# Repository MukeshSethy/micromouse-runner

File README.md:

# Micromouse Runner

A competition-style micromouse robot on a custom **100 × 120 mm, 4-layer**
KiCad 10 PCB: ESP32-S3 module doing all control + wireless telemetry, a 2S
power tree with a regulated 6 V motor rail, a BNO055 9-axis IMU, research-
verified sensor geometry, and a fully script-generated, fully autorouted design.

 > **Status (2026-07-20, rev 7.2): all requirements closed — fab-ready, order-ready.**
> `verify_drc.py` PASS: **0 errors / 0 warnings / 0 unconnected / 0 parity /
> ratsnest 0** (error-inclusive severity — never use `--severity-warning`,
> it hides errors on KiCad 10.0.4). Final battery: **12/12 green** (ERC,
> netlist gates, 41 circuit tests, 30-pin fw gate, flash/preflight/power/hw/
> line sims incl. IMU self-test coverage, 4/4 negative tests, DRC).
> Rev 7.2 adds: **XT60 battery input** (parallel with JST-XH, ONE PACK ONLY),
> **buzzer on IO46**, **JST-ZH motor connectors** (the robu GA12-N20 factory
> plug goes straight in — zero soldering), optional balance lead, selective
> silk refdes + assembly-PDF debug maps. Production folders for **Lion
> Circuits** ([`pcb/LionCircuit_4layers/`](pcb/LionCircuit_4layers/)) and
> **JLCPCB** ([`pcb/JLCPCB_4layers/`](pcb/JLCPCB_4layers/)). A leaner
> **2-layer, fully JLC-assemblable** edition (line sensors removed) is under
> construction at [`pcb/JLCPCB_2layers/`](pcb/JLCPCB_2layers/). Each project
> folder is self-contained: `design/`, `production/`, `fw/`, `simulation/`,
> `images/`.

**Top** — sensors, module, connectors (motor plugs go straight into J5/J6):

**Bottom** — ground pour, USB ESD cluster, button-side routing:

## The board (rev 7)

| Subsystem | Part | Notes |
|---|---|---|
| Controller | ESP32-S3-WROOM-1-N8R2 (bare module, dual-core FreeRTOS) | Rear placement; antenna spans a rear-edge U-notch (Espressif fallback), tip inside the board |
| Motor driver | TB6612FNG bare SSOP-24, **IN/IN PWM mode** | 6 V VM rail; PWMA/PWMB/STBY tied high, the four IN pins carry LEDC |
| **Power** | **2S LiPo** → **AP63203** (3.3 V/2 A logic) + **TPS54302** (regulated **6.0 V**/3 A motors) | Fuse 3.5 A/16 V PPTC (rev 7.1), DMP3098L reverse P-FET (Vgs ±20 V), balance-tap per-cell monitoring (optional — fw auto-detects); battery via JST-XH **or** XT60 (rev 7.2, ONE PACK ONLY) |
| **Switches** | **SW5 = PWR ALL** (logic EN) + **SW6 = PWR MOTORS** (6 V rail EN) | Motors need both on; SW6's pull-up feeds from the SW5 node |
| **IMU** | **BNO055 9-axis** on the centerline, I2C (IO18/21), INT IO37 | Internal oscillator; gyro drives the yaw loop |
| Wall sensors | 6× IR333-A + PT334-6B pairs: front **0°**, diagonal **45.0°**, side **90.0°** | Exact aims with silk angle callouts; bent-body outlines fully inside the board (3–5 mm edge gap) |
| Line sensors | 8× Vishay TCRT5000, 9.525 mm QTR pitch, bottom face | Read through a CD74HC4067 mux (+ battery/VBUS telemetry on spare channels); walls go **direct to ADC1** |
| Indicators | Per-sensor LEDs on top for all 8 line + 6 wall channels | Wall LED ON = wall seen |
| User I/O | Buttons **A / B / C** (+ RST) lettered on silk; two power slides | A doubles as BOOT |
| USB | USB-C at the rear (flash/debug), ESD-protected, VBUS cable-detect | Direct D± (no series R, Espressif practice); 1×6 JTAG header |

All parts are orderable from **Lion Circuits** (verified In-Stock, 2026-07);
see [`pcb/STANDARDS.md`](pcb/STANDARDS.md) for the impedance / IPC / Espressif
compliance write-up.

Drive wheels run in open edge notches (wheel/tyre width unconstrained);
front castor hole at the nose. Chamfered nose for the diagonal sensor pair.

### 3D-printable motor bracket

Print two of the UKMARSBot **Pololu-pattern N20 bracket** (MIT licence):
[`pololu-gear-motor-bracket-standard.stl`](https://raw.githubusercontent.com/ukmars/ukmarsbot/master/mechanical/pololu-gear-motor-bracket-standard.stl)
(from [github.com/ukmars/ukmarsbot](https://github.com/ukmars/ukmarsbot),
`mechanical/`). The board is drilled for it: Ø3.2 mm NPTH pairs at 18.0 mm
centres — (17.25, 75)/(17.25, 93) and (82.75, 75)/(82.75, 93), axle at y = 84.
M2/M2.5/M3 screws from the underside into nuts captured by the bracket.

## Design rules & tooling

- 0.3 mm clearance against **every through-hole pin** on every verification
  path (hand-solder safety, structural in the router); SMD fields may relax
  to 0.16 mm where physics demands it.
- GND poured on F.Cu (full board) + B.Cu (remainder) + the In1 plane; In2 =
  3V3 plane; VM_BATT/VM_6V as priority-1 B.Cu islands; SMD pour pads stitched.
- Routed to **zero unrouted edges** by the project's own 4-layer A*
  autorouter (`route_loaded.py`): jailed-first ordering with immediate retry
  ladders, hand-computed bridges for the USB-C pad field, wide
  "verify-proof" retry rungs, and a convergent DRC heal loop
  (`heal_all.py`). The war stories live in `pcb/PROJECT_NOTES.md`.

## Repository layout

```
micromouse-runner/
├── pcb/            KiCad hardware design
│   ├── micromouse-pcb.kicad_sch / .kicad_pcb / .kicad_pro
│   ├── netlist.net
│   ├── CONNECTIONS.md      every net, every pin, and why (generated, coverage-enforced)
│   ├── PROJECT_NOTES.md    full design decision log, research, and known issues
│   ├── n20.pretty/         hand-authored exact N20 motor footprint + 3D model
│   └── tools/              generators (schematic + PCB are script-produced, so auditable)
│       ├── gen_sch.py / build_schematic.py     schematic generator
│       ├── gen_pcb.py / build_pcb.py           placement + in-house N-layer A* autorouter
│       ├── board_geom.py                       single source of mechanical truth
│       ├── route_loaded.py                     routing pipeline (run build_pcb.py first)
│       ├── heal_all.py                         convergent DRC-unconnected healer
│       └── gen_connections.py / verify_netlist.py   docs + connectivity checks
├── fw/             sample firmware + host simulation
│   ├── micromouse/     pins.h (netlist-gated) + control_core + .ino (line following)
│   ├── sim/            gcc host sim of the EXACT control core (scenarios asserted)
│   └── check_pins.py   gate: every firmware pin verified against the netlist
├── simulation/     maze-solving / motion simulation — planned
└── images/         renders
```

## Verification

- `pcb/TEST_REPORT.md` — **41** analytical circuit tests computed from the
  netlist (2S power tree, both bucks + the dual-switch enable logic, IN/IN
  motor drive, IMU I2C, mux telemetry, flashing/straps/JTAG, every IR chain),
  100 % net + component coverage. The harness **caught a real design bug**
  (the motor rail could never enable — R69's 1 MΩ source impedance sagged the
  EN divider; fixed).
- `pcb/STANDARDS.md` — impedance / IPC-2221B / IPC-2152 / grounding /
  Espressif antenna compliance, with numbers (USB-FS is not a
  controlled-impedance case; the 90 Ω rule is high-speed-only).
- `pcb/TRACE_REPORT.md` — trace-level copper analysis of the routed board:
  per-net path resistance, IR drops at operating currents, via ampacity, USB
  skew.
- `fw/sim/` — the shipped control core runs against board-derived physics;
  the sim caught two real control bugs before hardware. All scenarios pass.
- `pcb/CONNECTIONS.md` — the per-trace justification document: every net,
  every pin, and why (generated, coverage-enforced).

> **Connectivity note:** `kicad-cli pcb drc` under-reports unconnected items
> headless; the project gates on the **pcbnew ratsnest** (`GetUnconnectedCount`
> after a zone fill), and `finalize.py` refuses to strip copper unless that
> ratsnest is already zero.

## Ordering / fabrication

- `pcb/BOM.csv` — every row a verified MPN **In-Stock at Lion Circuits**
  (turnkey from Digi-Key/Mouser/Element14/Arrow/Avnet/RS). Power: AP63203WU-7,
  TPS54302DDCR, DMP3098L-7, MINISMDC260F/16-2, SRP4020TA-4R7M, EEE-FT1C221AP.
  IMU: BNO055. Optics: IR333-A + PT334-6B + TCRT5000. Connectors/switches:
  USB4105-GF-A, B2B-XH-A, PCM12SMTR, PTS645VL582LFS.
- `pcb/tools/export_fab.py` regenerates `pcb/fab/`: gerbers, Excellon drill
  (bracket/castor NPTH tools asserted present), placement CSV, and a fit-check
  STEP that loads **every** 3D model (project-local box-true models for the
  N20 motors, BNO055 and the SRP4020TA inductors).

## Build / regenerate

The PCB tooling runs from `pcb/` using the KiCad-bundled Python (`pcbnew`);
see `pcb/PROJECT_NOTES.md` for exact commands and the many hard-won
KiCad-format notes. Regeneration order: `build_schematic.py` → export
netlist → `verify_netlist.py` → `build_pcb.py` → `route_loaded.py` →
`heal_all.py` → `finalize.py` (silk→fab + ratsnest-gated stub cleanup) →
`sync_board_meta.py` (parity metadata) → `export_fab.py`.

> **Warning:** the shipped rev-7 board was refined **in-place** after routing;
> regenerating overwrites it with a re-route that must then re-pass
> `pcb/tools/verify_drc.py`. Do not regenerate casually — the committed
> `.kicad_pcb` is the verified artifact.

## Status

**Rev 7 ships fully routed and verified — all requirements closed.**
`verify_drc.py` PASS: 0 errors / 0 warnings / 0 unconnected / 0 parity /
ratsnest 0 · ERC 0 · 41/41 circuit tests · 29/29 pins · sim ALL PASS ·
export_fab ALL GATES. 2S power with a regulated 6 V motor rail, dual switches,
BNO055 IMU on the centre line, exact 0/45/90° wall-sensor aims with the front
sensors nested in the line-array gaps, indicators behind the sensors, ESP32
decoupling at the pin, ground poured on every possible layer, and a Lion
Circuits-orderable BOM. Formal requirement tracking:
[`pcb/REQUIREMENTS.md`](pcb/REQUIREMENTS.md).

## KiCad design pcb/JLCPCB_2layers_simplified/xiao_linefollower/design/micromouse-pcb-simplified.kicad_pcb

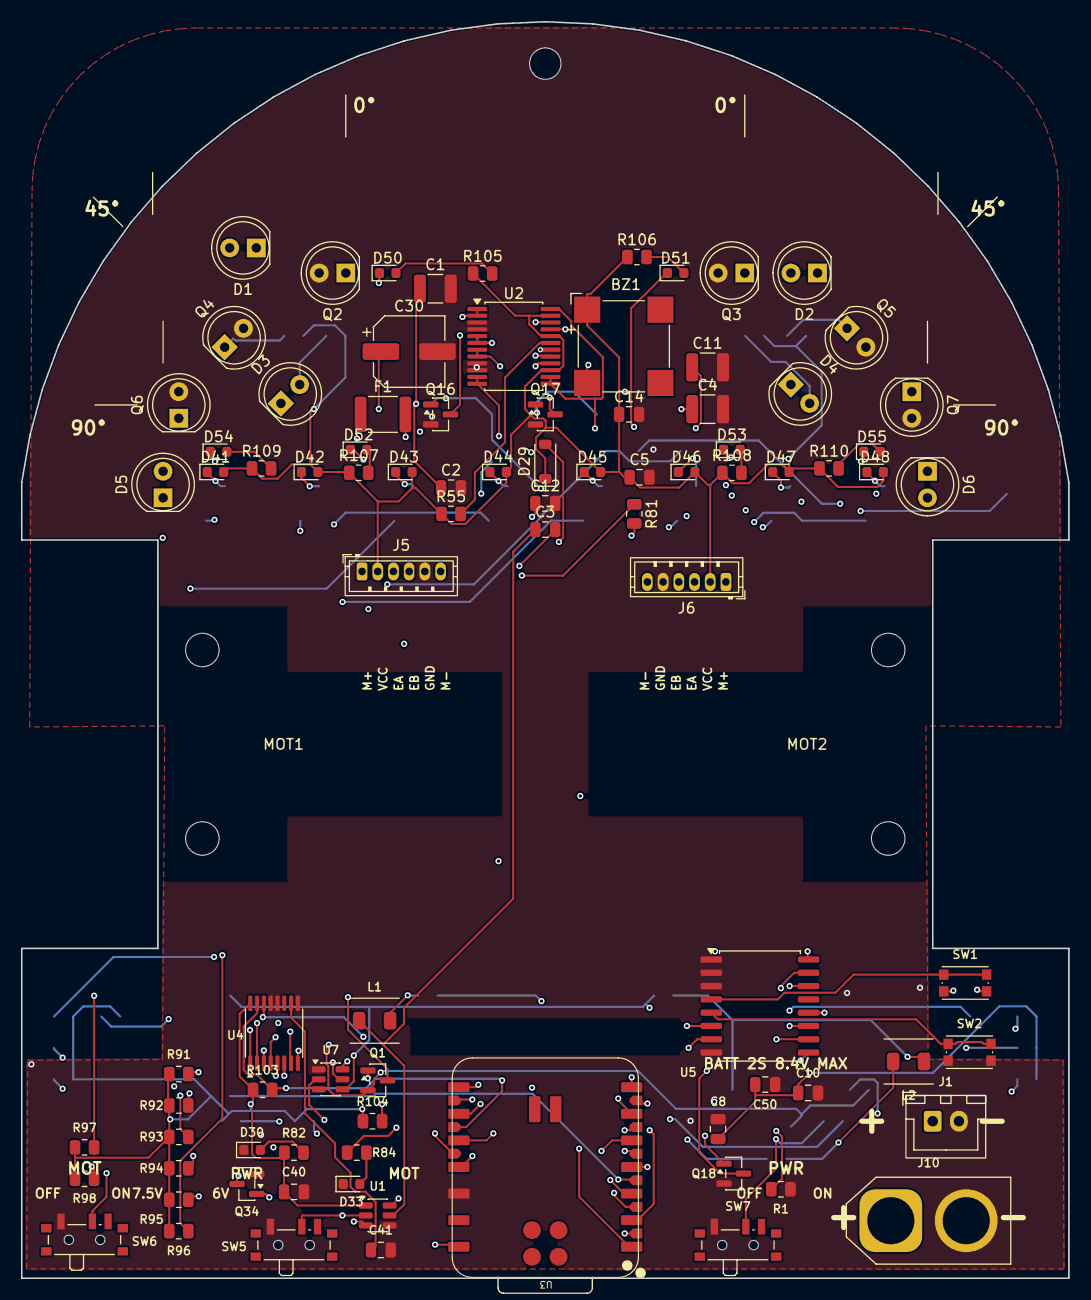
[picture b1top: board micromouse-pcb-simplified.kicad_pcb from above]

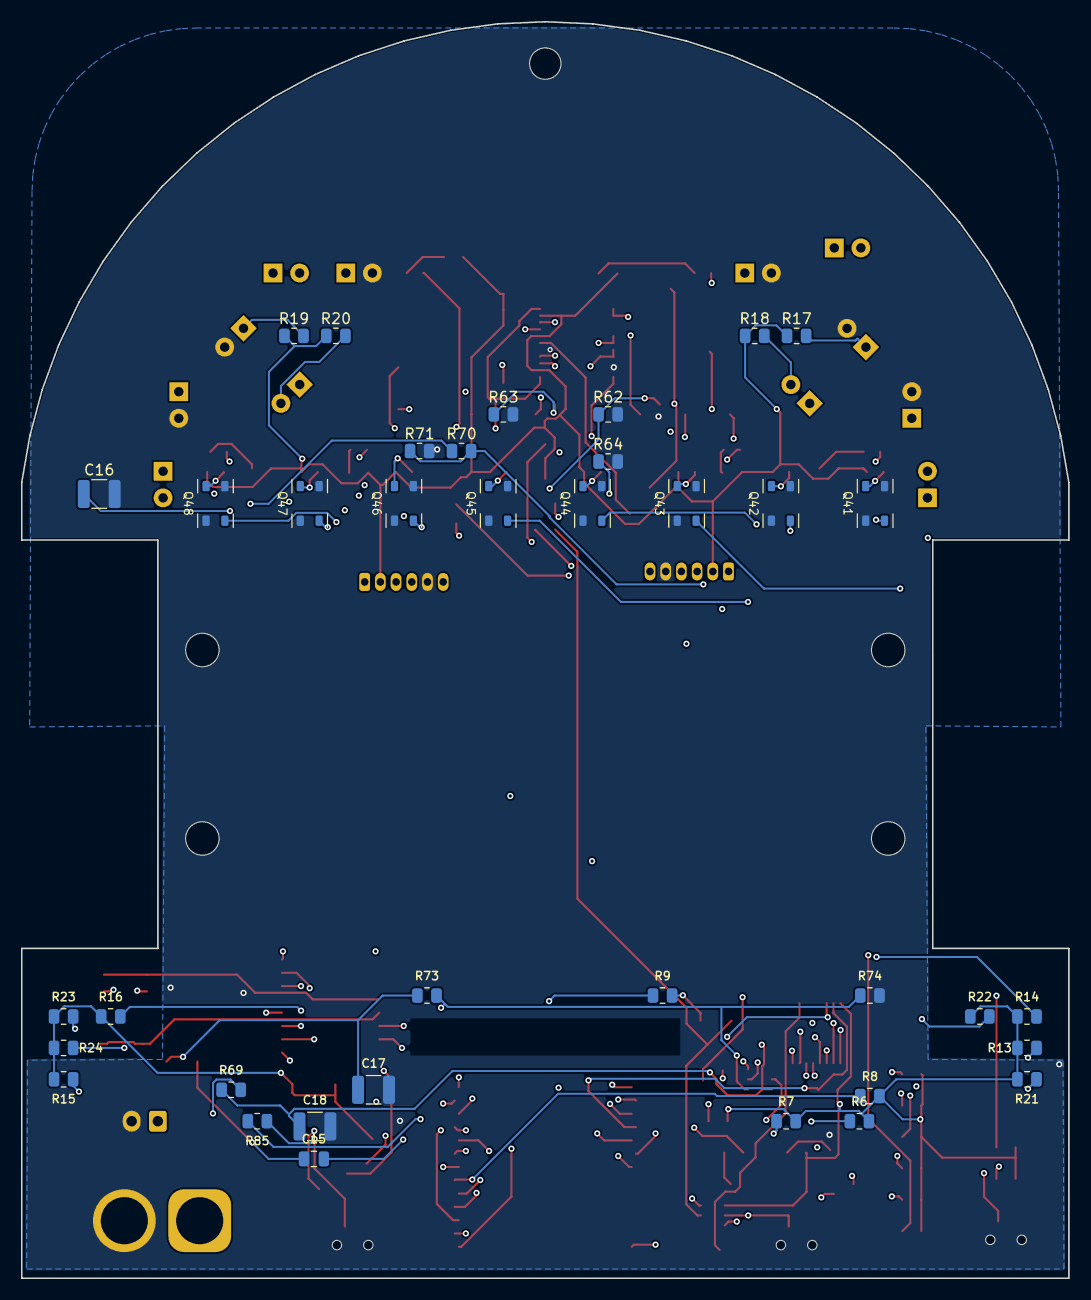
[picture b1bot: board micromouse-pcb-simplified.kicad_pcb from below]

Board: 4 copper layers, 100.0 x 120.0 mm, 133 parts (38 on the bottom side), 84 nets.

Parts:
BZ1: MagneticBuzzer_CUI_CMT-8504-100-SMT
C1, C4, C11, C18: 10uF/25V; C_1210_3225Metric
C2, C3, C12, C14, C15: 100nF; C_0805_2012Metric
C5: 22uF; C_0805_2012Metric
C8, C10, C40, C41, C50: C_0805_2012Metric
C16, C17: 22uF/25V; C_1210_3225Metric
C30: 220uF/16V; CP_Elec_6.3x7.7
CW1: CastorWheel
D1, D2, D3, D4, D5, D6: LED_D5.0mm_IRGrey
D29: D_SOD-123
D30, D33, D41, D42, D43, D44, D45, D46, D47, D48: LED_0603_1608Metric
D50, D51, D52, D53, D54, D55: APT1608SGC; LED_0603_1608Metric
F1: Fuse_1812_4532Metric
H1, H2, H3, H4, H5: MountingHole_NPTH
J1: JST_XH_B2B-XH-A_1x02_P2.50mm_Vertical
J5, J6: JST_ZH_B6B-ZR_1x06_P1.50mm_Vertical
J10: AMASS_XT60-M_1x02_P7.20mm_Vertical
L1, L2: 4.7uH; L_Bourns_SRP4020TA
MOT1, MOT2: N20_Motor_Encoder
Q1, Q16, Q17, Q18, Q34: SOT-23
Q2, Q3, Q4, Q5, Q6, Q7: LED_D5.0mm_IRBlack
Q41, Q42, Q43, Q44, Q45, Q46, Q47, Q48: VAL; QRE1113GR
R1, R6, R7, R8, R9, R13, R14, R15, R16, R17, R18, R19, R20, R21, R22, R23, R24, R55, R62, R63, R64, R69, R70, R71, R73, R74, R81, R82, R84, R85, R91, R92, R93, R94, R95, R96, R97, R98, R103, R104: R_0805_2012Metric
R105, R106, R107, R108, R109, R110: 220; R_0805_2012Metric
SW1, SW2: SW_Push_1P1T_NO_CK_KMR2
SW5, SW6, SW7: SW_SPDT_PCM12
U1: TSOT-23-6
U2: SSOP-24_5.3x8.2mm_P0.65mm
U3: XIAO-nRF52840-Plus-SMD
U4: TSSOP-16_4.4x5mm_P0.65mm
U5: SOIC-16W_7.5x10.3mm_P1.27mm
U7: SOT-23-6

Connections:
AIN1: U2.21, U3.7
AIN2: U2.22, U3.8
BATT_RAW: F1.1, J1.1, J10.1
BIN1: U2.17, U3.9
BIN2: U2.16, U3.10
BUZZ_CTRL: R81.1, U3.11
BUZZ_DRV: BZ1.2, D29.2, Q34.3
EMIT_DIAG_K: D3.1, D4.1, Q17.3
EMIT_FRONT_K: D1.1, D2.1, Q16.3
EMIT_SIDE_K: D5.1, D6.1, Q18.3
ENC1_A: J5.3, R6.1, U3.15
ENC1_B: J5.4, R7.1, U3.16
ENC2_A: J6.3, R8.1, U3.17
ENC2_B: J6.4, R9.1, U3.18
FB_6V: R73.2, R74.1, R85.1, U7.4
GND: C1.2, C2.2, C4.2, C5.2, C8.2, C10.2, C11.2, C12.2, C14.2, C16.2, C17.2, C18.2, C30.2, C40.2, C41.2, C50.2, D30.1, D33.1, J1.2, J5.5, J6.5, J10.2, Q2.2, Q3.2, Q4.2, Q5.2, Q6.2, Q7.2, Q16.2, Q17.2, Q18.2, Q34.2, Q41.2, Q41.4, Q42.2, Q42.4, Q43.2, Q43.4, Q44.2, Q44.4, Q45.2, Q45.4, Q46.2, Q46.4, Q47.2, Q47.4, Q48.2, Q48.4, R1.2, R62.2, R63.2, R64.2, R71.2, R74.2, SW1.2, SW2.2, SW5.1, SW6.1, SW7.1, U1.4, U2.3, U2.4, U2.9, U2.10, U2.18, U3.12, U4.9, U4.12, U4.13, U5.1, U5.2, U5.3, U5.8, U7.1
LINE0_ADC: D41.1, Q41.3, U4.1
LINE1_ADC: D42.1, Q42.3, U4.2
LINE2_ADC: D43.1, Q43.3, U4.3
LINE3_ADC: D44.1, Q44.3, U4.4
LINE4_ADC: D45.1, Q45.3, U4.5
LINE5_ADC: D46.1, Q46.3, U4.6
LINE6_ADC: D47.1, Q47.3, U4.7
LINE7_ADC: D48.1, Q48.3, U4.8
MOTA_N: J5.6, U2.5, U2.6
MOTA_P: J5.1, U2.1, U2.2
MOTB_N: J6.6, U2.7, U2.8
MOTB_P: J6.1, U2.11, U2.12
MOTLED_A: D33.2, R84.2
MOT_EN: R70.2, R71.1, SW6.2, U7.5
unnamed: D1.2, R14.2
unnamed: D2.2, R16.2
unnamed: D3.2, R18.2
unnamed: D4.2, R20.2
unnamed: D5.2, R22.2
unnamed: D6.2, R24.2
unnamed: D50.2, R105.2
unnamed: D51.2, R106.2
unnamed: D52.2, R107.2
unnamed: D53.2, R108.2
unnamed: D54.2, R109.2
unnamed: D55.2, R110.2
unnamed: F1.2, Q1.3
unnamed: Q1.1, R1.1
unnamed: Q34.1, R81.2
unnamed: Q41.1, R91.2
unnamed: Q42.1, R92.2
unnamed: Q43.1, R93.2
unnamed: Q44.1, R94.2
unnamed: Q45.1, R95.2
unnamed: Q46.1, R96.2
unnamed: Q47.1, R97.2
unnamed: Q48.1, R98.2
unnamed: R85.2, SW7.2
unnamed: C3.2, U1.6
unnamed: R55.2, U2.19
unnamed: C41.1, U4.10
unnamed: SW1.1, U5.4
unnamed: SW2.1, U5.5
unnamed: C15.2, U7.6
PLUS3V3: BZ1.1, C5.1, C8.1, C10.1, C14.1, C40.1, C50.1, D29.1, D41.2, D42.2, D43.2, D44.2, D45.2, D46.2, D47.2, D48.2, J5.2, J6.2, L1.2, R6.2, R7.2, R8.2, R9.2, R13.1, R14.1, R15.1, R16.1, R17.1, R18.1, R19.1, R20.1, R21.1, R22.1, R23.1, R24.1, R55.1, R82.1, R91.1, R92.1, R93.1, R94.1, R95.1, R96.1, R97.1, R98.1, R103.1, R104.1, R105.1, R106.1, R107.1, R108.1, R109.1, R110.1, U1.1, U2.15, U2.20, U2.23, U3.14, U4.16, U5.16
PWRLED_A: D30.2, R82.2
PWR_EN: R69.2, R70.1, SW5.2, U1.2
SCL: R104.2, U3.23, U4.14, U5.14
SDA: R103.2, U3.22, U4.15, U5.15
SW_3V3: C3.1, L1.1, U1.5
SW_6V: C15.1, L2.1, U7.2
VM_6V: C11.1, C12.1, C16.1, C17.1, C30.1, L2.2, R73.1, R84.1, U2.13, U2.14, U2.24
VM_BATT: C1.1, C2.1, C4.1, C18.1, Q1.2, R69.1, U1.3, U7.3
WALL_DL_LED: D52.1, U5.9
WALL_DL_SENSE: Q4.1, R17.2, U3.3
WALL_DR_LED: D53.1, U5.10
WALL_DR_SENSE: Q5.1, R19.2, U3.4
WALL_EMIT_DIAG: Q17.1, R63.1, U3.20
WALL_EMIT_FRONT: Q16.1, R62.1, U3.19
WALL_EMIT_SIDE: Q18.1, R64.1, U3.21
WALL_FL_LED: D50.1, U5.6
WALL_FL_SENSE: Q2.1, R13.2, U3.1
WALL_FR_LED: D51.1, U5.7
WALL_FR_SENSE: Q3.1, R15.2, U3.2
WALL_SL_LED: D54.1, U5.11
WALL_SL_SENSE: Q6.1, R21.2, U3.5
WALL_SR_LED: D55.1, U5.12
WALL_SR_SENSE: Q7.1, R23.2, U3.6

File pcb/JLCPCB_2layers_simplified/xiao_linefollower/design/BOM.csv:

Reference,Value,Footprint,Qty,MPN,Manufacturer
BZ1,"CMT-8504-100-SMT (magnetic transducer 8.5mm, 15R coil, 4kHz; pads 3/4 are mechanical dummies)",Buzzer_Beeper:MagneticBuzzer_CUI_CMT-8504-100-SMT,1,CMT-8504-100-SMT-TR,Same Sky (CUI Devices)
"C1,C4,C11,C18",10uF/25V,Capacitor_SMD:C_1210_3225Metric,4,CL32B106KBJNNNE,Samsung Electro-Mechanics
"C2,C3,C8,C12,C14,C15,C40,C41,C50",100nF,Capacitor_SMD:C_0805_2012Metric,9,CL21B104KBCNNNC,Samsung Electro-Mechanics
C5,22uF,Capacitor_SMD:C_0805_2012Metric,1,CL21A226KPCLRNC,Samsung Electro-Mechanics
C10,10uF,Capacitor_SMD:C_0805_2012Metric,1,CL21A106KPFNNNE,Samsung Electro-Mechanics
"C16,C17",22uF/25V,Capacitor_SMD:C_1210_3225Metric,2,CL32A226KAJNNNE,Samsung Electro-Mechanics
C30,220uF/16V,Capacitor_SMD:CP_Elec_6.3x7.7,1,EEE-FT1C221AP,Panasonic
"D1,D2,D3,D4,D5,D6",IR333-A (Everlight 5mm 940nm 20deg; LD271 base symbol; TSAL6400 is lifecycle-Obsolete at Lion),LED_THT:LED_D5.0mm_IRGrey,6,IR333-A,Everlight
D29,1N4148W (flyback clamp across the buzzer coil),Diode_SMD:D_SOD-123,1,1N4148W-7-F,Diodes Incorporated
"D30,D33,D41,D42,D43,D44,D45,D46,D47,D48",Power LED 0603 red (JLC good-stock),LED_SMD:LED_0603_1608Metric,10,APT1608SURCK,Kingbright
"D50,D51,D52,D53,D54,D55",WALL_DL_LED wall-detection indicator (0603 green LED; firmware drives the PCF8574 pin LOW via I2C when this sensor's ADC reading crosses its wall-detected threshold),LED_SMD:LED_0603_1608Metric,6,APT1608SGC,Kingbright
F1,2.6A/16V PPTC,Fuse:Fuse_1812_4532Metric,1,MINISMDC260F/16-2,Littelfuse
J1,BATT_IN_2S,Connector_JST:JST_XH_B2B-XH-A_1x02_P2.50mm_Vertical,1,B2B-XH-A,JST
"J5,J6",MOTOR_A_N20_ENCODER,Connector_JST:JST_ZH_B6B-ZR_1x06_P1.50mm_Vertical,2,B6B-ZR(LF)(SN),JST
J10,BATT_IN_XT60 (parallel option -- ONE PACK ONLY),Connector_AMASS:AMASS_XT60-M_1x02_P7.20mm_Vertical,1,XT60-M,AMASS
"L1,L2",4.7uH,n20:L_Bourns_SRP4020TA,2,SRP4020TA-4R7M,Bourns
Q1,"Q_PMOS reverse guard (DMP3098L-7: Vgs +/-20V, 2S-safe)",Package_TO_SOT_SMD:SOT-23,1,DMP3098L-7,Diodes Incorporated
"Q2,Q3,Q4,Q5,Q6,Q7",PT334-6B (5mm filtered PT; LONG LEAD = EMITTER; SFH309 base symbol so ERC checks pins),LED_THT:LED_D5.0mm_IRBlack,6,PT334-6B,Everlight
"Q16,Q17,Q18",BSS138 (real part; Q_NMOS_GSD base symbol used so ERC checks pins),Package_TO_SOT_SMD:SOT-23,3,BSS138LT1G,onsemi
Q34,MMBT2222A (buzzer low-side driver; Q_NPN_BEC base symbol so ERC checks pins),Package_TO_SOT_SMD:SOT-23,1,MMBT2222A-7-F,Diodes Incorporated
"Q41,Q42,Q43,Q44,Q45,Q46,Q47,Q48","QRE1113GR (onsemi SMT reflective sensor; Pololu QTR sensor part; pin1=Anode pin2=Cathode(IR LED) pin3=Collector pin4=Emitter(phototransistor); B.Cu placement, faces the floor)",qre1113:QRE1113GR,8,QRE1113GR,onsemi
"R1,R62,R63,R64,R69,R73",100k,Resistor_SMD:R_0805_2012Metric,6,RC0805FR-07100KL,Yageo
"R6,R7,R8,R9,R55",10k,Resistor_SMD:R_0805_2012Metric,5,WR08X1002FTL,Walsin
"R13,R15,R17,R19,R21,R23",47k,Resistor_SMD:R_0805_2012Metric,6,RC0805FR-0747KL,Yageo
"R14,R16,R18,R20,R22,R24",33,Resistor_SMD:R_0805_2012Metric,6,RC0805FR-0733RL,Yageo
R70,220k,Resistor_SMD:R_0805_2012Metric,1,RC0805FR-07220KL,Yageo
R71,110k,Resistor_SMD:R_0805_2012Metric,1,RC0805FR-07110KL,Yageo
R74,11k,Resistor_SMD:R_0805_2012Metric,1,RC0805FR-0711KL,Yageo
"R81,R91,R92,R93,R94,R95,R96,R97,R98,R105,R106,R107,R108,R109,R110",220,Resistor_SMD:R_0805_2012Metric,15,RC0805FR-07220RL,Yageo
"R82,R84",1k,Resistor_SMD:R_0805_2012Metric,2,RC0805FR-071KL,Yageo
R85,40.2k,Resistor_SMD:R_0805_2012Metric,1,RC0805FR-0740K2L,Yageo
"R103,R104",2.2k,Resistor_SMD:R_0805_2012Metric,2,RC0805FR-072K2L,Yageo
"SW1,SW2",Tactile pushbutton switch,Button_Switch_SMD:SW_Push_1P1T_NO_CK_KMR2,2,KMR221NGLFS,C&K
"SW5,SW6,SW7",PWR ALL (PCM12SMTR slide; slide-to-GND = OFF),Button_Switch_SMD:SW_SPDT_PCM12,3,PCM12SMTR,C&K
U1,AP63203WU-7 (fixed 3.3V 2A buck; AP63200WU base symbol so ERC checks pins),Package_TO_SOT_SMD:TSOT-23-6,1,AP63203WU-7,Diodes Incorporated
U2,TB6612FNG,Package_SO:SSOP-24_5.3x8.2mm_P0.65mm,1,"TB6612FNG,C,8,EL",Toshiba
U3,"Seeed XIAO nRF52840 Sense Plus (SKU 102010694): D0-D5 ADC-capable, D6-D10 + 9 Plus pads digital-only. Own onboard IMU/RGB LED/USB-C/reset button.",xiao:XIAO-nRF52840-Plus-SMD,1,"102010694 (Seeed XIAO nRF52840 Sense Plus -- HAND-SOLDER, NOT part of turnkey SMT assembly)",Seeed Studio
U4,"ADS7830IPWR (I2C 8-ch 8-bit ADC, TSSOP-16; A0=A1=GND -> addr 0x48; internal 2.5V ref; single-ended mode, COM unused)",Package_SO:TSSOP-16_4.4x5mm_P0.65mm,1,ADS7830IPWR,Texas Instruments
U5,"PCF8574DWR (8-bit I2C GPIO expander, SOIC-16W; A0=A1=A2=GND -> addr 0x20/0x21; TCA9534 base symbol so ERC checks pins -- see comment above)",Package_SO:SOIC-16W_7.5x10.3mm_P1.27mm,1,PCF8574DWR,Texas Instruments
U7,TPS54302DDCR (6.0V/3A motor buck; FB=100k/11k),Package_TO_SOT_SMD:SOT-23-6,1,TPS54302DDCR,Texas Instruments

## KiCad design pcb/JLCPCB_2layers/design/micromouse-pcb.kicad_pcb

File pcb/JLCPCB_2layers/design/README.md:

# JLCPCB 2-layer micromouse — design (work in progress)

Derived from the 4-layer board, re-worked for JLCPCB full turnkey assembly:
- **2 layers** (not 4)
- **line sensors removed** (LS1–LS8 + their indicator LEDs / dependencies)
- **only JLC-assemblable parts** (no hand-solder step)

Status: under construction.

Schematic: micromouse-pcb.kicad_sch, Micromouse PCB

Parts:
BZ1: CMT-8504-100-SMT (magnetic transducer 8.5mm, 15R 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; MagneticBuzzer_CUI_CMT-8504-100-SMT; MPN CMT-8504-100-SMT-TR
C1, C4, C11, C18: 10uF/25V; C_1210_3225Metric; MPN CL32B106KBJNNNE
C2, C3, C6, C8, C12, C14, C15, C20, C23, C31: 100nF; C_0805_2012Metric; MPN CL21B104KBCNNNC
C5, C7: 22uF; C_0805_2012Metric; MPN CL21A226KPCLRNC
C9: 1uF; C_0805_2012Metric; MPN CL21B105KAFNNNE
C10, C24: 10uF; C_0805_2012Metric; MPN CL21A106KPFNNNE
C16, C17: 22uF/25V; C_1210_3225Metric; MPN CL32A226KAJNNNE
C30: 220uF/16V; CP_Elec_6.3x7.7; MPN EEE-FT1C221AP
D1, D2, D3, D4, D5, D6: IR333-A (Everlight 5mm 940nm 20deg; LD271 base sy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; LED_D5.0mm_IRGrey; MPN IR333-A
D23, D24, D25, D26, D27, D28: Indicator LED 0603 super-red AlInGaP, high-eff bi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; LED_0603_1608Metric; MPN APT1608SURCK
D29: 1N4148W (flyback clamp across the buzzer coil); D_SOD-123; MPN 1N4148W-7-F
D30: Power LED 0603 red (JLC good-stock); LED_0603_1608Metric; MPN APT1608SURCK
D31: Status LED 0603 red (JLC good-stock); LED_0603_1608Metric; MPN APT1608SURCK
D32: WS2812B addressable RGB 5050 (JLC good-stock); LED_WS2812B_PLCC4_5.0x5.0mm_P3.2mm; MPN XL-5050RGBC-WS2812B
D33: Motor-power LED 0603 (VM_6V present; JLC good-sto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; LED_0603_1608Metric; MPN APT1608SURCK
F1: 2.6A/16V PPTC; Fuse_1812_4532Metric; MPN MINISMDC260F/16-2
J1: BATT_IN_2S; JST_XH_B2B-XH-A_1x02_P2.50mm_Vertical; MPN B2B-XH-A
J5: MOTOR_A_N20_ENCODER; JST_ZH_B6B-ZR_1x06_P1.50mm_Vertical; MPN B6B-ZR(LF)(SN)
J6: MOTOR_B_N20_ENCODER; JST_ZH_B6B-ZR_1x06_P1.50mm_Vertical; MPN B6B-ZR(LF)(SN)
J7: USB-C rear (GCT USB4105; VBUS unused -- battery p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; USB_C_Receptacle_GCT_USB4105-xx-A_16P_TopMnt_Horizontal; MPN USB4105-GF-A
J10: BATT_IN_XT60 (parallel option -- ONE PACK ONLY); AMASS_XT60-M_1x02_P7.20mm_Vertical; MPN XT60-M
L1, L2: 4.7uH; L_Bourns_SRP4020TA; MPN SRP4020TA-4R7M
Q1: Q_PMOS reverse guard (DMP3098L-7: Vgs +/-20V, 2S-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; SOT-23; MPN DMP3098L-7
Q2, Q3, Q4, Q5, Q6, Q7: PT334-6B (5mm filtered PT; LONG LEAD = EMITTER; S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; LED_D5.0mm_IRBlack; MPN PT334-6B
Q16, Q17, Q18: BSS138 (real part; Q_NMOS_GSD base symbol used so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; SOT-23; MPN BSS138LT1G
Q28, Q29, Q30, Q31, Q32, Q33: BSS84 (PMOS indicator driver; Q_PMOS base symbol); SOT-23; MPN BSS84LT1G
Q34: MMBT2222A (buzzer low-side driver; Q_NPN_BEC base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; SOT-23; MPN MMBT2222A-7-F
R1, R2, R62, R63, R64, R69, R73: 100k; R_0805_2012Metric; MPN RC0805FR-07100KL
R3: 39k; R_0805_2012Metric; MPN RC0805FR-0739KL
R6, R7, R8, R9, R10, R11, R55, R65, R67, R79, R80: 10k; R_0805_2012Metric; MPN WR08X1002FTL
R12, R56: 5.1k; R_0805_2012Metric; MPN RC0805FR-075K1L
R13, R15, R17, R19, R21, R23: 47k; R_0805_2012Metric; MPN RC0805FR-0747KL
R14, R16, R18, R20, R22, R24: 33; R_0805_2012Metric; MPN RC0805FR-0733RL
R49, R50, R51, R52, R53, R54, R57, R58, R82, R83, R84: 1k; R_0805_2012Metric; MPN RC0805FR-071KL
R68: 15k; R_0805_2012Metric; MPN RC0805FR-0715KL
R70: 220k; R_0805_2012Metric; MPN RC0805FR-07220KL
R71: 110k; R_0805_2012Metric; MPN RC0805FR-07110KL
R74: 11k; R_0805_2012Metric; MPN RC0805FR-0711KL
R77, R78: 4.7k; R_0805_2012Metric; MPN RC0805FR-074K7L
R81: 220; R_0805_2012Metric; MPN RC0805FR-07220RL
SW1: BTN_A (start / BOOT); SW_Push_1P1T_NO_CK_KMR2; MPN KMR221NGLFS
SW2: BTN_B; SW_Push_1P1T_NO_CK_KMR2; MPN KMR221NGLFS
SW3: BTN_C; SW_Push_1P1T_NO_CK_KMR2; MPN KMR221NGLFS
SW4: RESET; SW_Push_1P1T_NO_CK_KMR2; MPN KMR221NGLFS
SW5: PWR ALL (PCM12SMTR slide; slide-to-GND = OFF); SW_SPDT_PCM12; MPN PCM12SMTR
SW6: PWR MOTORS (PCM12SMTR slide; slide-to-GND = motor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; SW_SPDT_PCM12; MPN PCM12SMTR
U1: AP63203WU-7 (fixed 3.3V 2A buck; AP63200WU base s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; TSOT-23-6; MPN AP63203WU-7
U2: TB6612FNG; SSOP-24_5.3x8.2mm_P0.65mm; MPN TB6612FNG,C,8,EL
U3: ESP32-S3-WROOM-1-N8R2 (quad PSRAM: IO35-37 usable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; ESP32-S3-WROOM-1; MPN ESP32-S3-WROOM-1-N8R2
U6: USBLC6-2SC6 (SOT-23-6; 2P6 base symbol so ERC che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; SOT-23-6; MPN USBLC6-2SC6
U7: TPS54302DDCR (6.0V/3A motor buck; FB=100k/11k); SOT-23-6; MPN TPS54302DDCR
U8: BNO055 (9-axis IMU + fusion; 3.3V native; I2C 0x2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; BNO055; MPN BNO055

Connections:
AIN1: U2.21 (AIN1), U3.19 (IO11)
AIN2: U2.22 (AIN2), U3.18 (IO10)
BATT_RAW: F1.1, J1.1, J10.1
BIN1: U2.17 (BIN1), U3.31 (IO38)
BIN2: R65.1, U2.16 (BIN2), U3.26 (IO45)
BUZZ_CTRL: R81.1, U3.16 (IO46)
BUZZ_DRV: BZ1.2 (-), D29.2 (A), Q34.3 (C)
EMIT_DIAG_K: D3.1 (K), D4.1 (K), Q17.3 (D)
EMIT_FRONT_K: D1.1 (K), D2.1 (K), Q16.3 (D)
EMIT_SIDE_K: D5.1 (K), D6.1 (K), Q18.3 (D)
ENC1_A: J5.3, R6.1, U3.24 (IO47)
ENC1_B: J5.4, R7.1, U3.25 (IO48)
ENC2_A_S3: R57.2, U3.36 (RXD0)
ENC2_B: J6.4, R9.1, R58.1
ENC2_B_S3: R58.2, U3.37 (TXD0)
ESP_EN: C9.1, R11.2, SW4.1, U3.3 (EN)
FB_6V: R73.2, R74.1, U7.4 (FB)
IMU_INT: U3.30 (IO37), U8.14 (INT)
IMU_SCL: R78.2, U3.23 (IO21), U8.19 (COM1)
IMU_SDA: R77.2, U3.11 (IO18), U8.20 (COM0)
MOTA_N: J5.6, U2.5 (AO2), U2.6 (AO2)
MOTA_P: J5.1, U2.1 (AO1), U2.2 (AO1)
MOTB_N: J6.6, U2.7 (BO2), U2.8 (BO2)
MOTB_P: J6.1, U2.11 (BO1), U2.12 (BO1)
MOTLED_A: D33.2 (A), R84.2
unnamed: D23.2 (A), R49.2
unnamed: D24.2 (A), R50.2
unnamed: D25.2 (A), R51.2
unnamed: D26.2 (A), R52.2
unnamed: D27.2 (A), R53.2
unnamed: D28.2 (A), R54.2
unnamed: J7.B5 (CC2), R56.1
unnamed: F1.2, Q1.3 (D)
unnamed: Q1.1 (G), R1.1
unnamed: Q34.1 (B), R81.2
unnamed: R55.2, U2.19 (STBY)
unnamed: C15.2, U7.6 (BOOT)
unnamed: C20.1, U8.9 (CAP)
unnamed: R79.2, U8.4 (~BOOT_LOAD_PIN)
unnamed: R80.2, U8.11 (~RESET)
PWRLED_A: D30.2 (A), R82.2
RGB_DATA: D32.4 (DIN), U3.22 (IO14)
STATLED_A: D31.2 (A), R83.2
STATUS_LED: R83.1, U3.20 (IO12)
SW_6V: C15.1, L2.1, U7.2 (SW)
USB_DM: U3.13 (USB_D-), U6.6 (I/O1)
USB_DM_C: J7.A7 (D-), J7.B7 (D-), U6.1 (I/O1)
USB_DP: U3.14 (USB_D+), U6.4 (I/O2)
USB_DP_C: J7.A6 (D+), J7.B6 (D+), U6.3 (I/O2)
USB_VBUS: J7.A4 (VBUS), J7.A9 (VBUS), J7.B4 (VBUS), J7.B9 (VBUS), R67.1
USER_BTN2: SW2.1, U3.28 (IO35)
USER_BTN3: SW3.1, U3.29 (IO36)
VBUS_SENSE: R67.2, R68.1, U3.17 (IO9)
WALL_EMIT_DIAG: Q17.1 (G), R63.1, U3.9 (IO16)
WALL_EMIT_FRONT: Q16.1 (G), R62.1, U3.8 (IO15)
WALL_EMIT_SIDE: Q18.1 (G), R64.1, U3.10 (IO17)

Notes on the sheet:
POWER -- 2S LiPo -> AP63203 3V3 (2A) + TPS54302 6V motor rail (3A); SW5=logic, SW6=motors
+3V3 is the regulated logic rail: ESP32-S3, mux, IMU, encoder VCC, PT pull-ups, indicator drivers and IR LED current. VM_6V feeds ONLY the TB6612 VM pins.
VBAT_SENSE = pack (0-8.4V) x 39/139 <= 2.36V on ADC1 IO7 (direct). VBUS_SENSE = 5V x 15/25 <= 3.15V on IO9. PACK-LEVEL monitoring only (per-cell/balance removed). Firmware cutoff: 6.6V pack floor (3.3V/cell avg); the 6V motor rail stays in regulation across the 6.6-8.4V window.
MOTOR DRIVER (TB6612FNG, SMD) -- 2x N20-with-encoder motors
Bare TB6612FNG (U2, SSOP-24) in IN/IN PWM mode: PWMA/PWMB tied 3V3, AIN/BIN = LEDC (IN1=PWM,IN2=0 fwd-coast; IN1=PWM,IN2=1 rev-brake). VM = regulated 6.0V rail (TPS54302, 3A limit) gated by SW6; STBY pulled high (R55) -- motor kill = SW6 + IN pins' internal pull-downs. Decoupling: C30 220uF/16V alu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
10k pull-ups on all 4 encoder lines -- defensive: N20-encoder wire-color-to- function mapping is unverified for the exact unit ordered (see PROJECT_NOTES.md), and encoder output stage (open-drain vs push-pull) isn't confirmed either. A pull-up is required if open-drain and harmless if push-pull. Re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
CONTROLLER -- ESP32-S3-WROOM-1 (dual-core 240MHz, FreeRTOS, WiFi): control + telemetry
ESP32-S3-WROOM-1 on FreeRTOS: 6 wall sensors DIRECT on ADC1 IO1-IO6 (a fired pair is sampled in parallel), line array via U4 (IO7 + IO11-13), battery IO8, TB6612 on IO9/10/38/45, buzzer IO46 (straps 45/46 = idle-low outputs ONLY -- never add pull-ups), encoders IO43/44/47/48 (PCNT hardware quadratu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
USER INTERFACE -- 3 buttons
Buttons are lettered on the silkscreen: A=SW1, B=SW2, C=SW3, RST=SW4. SW1/A = USER_BTN on IO0: start-run button AND the BOOT strap (hold A, tap RST -> ROM download mode). External 10k pull-up R10 keeps the strap solid. SW2/SW3 = USER_BTN2/3 on IO35/IO36 (menu/select UX): active-low, firmware enable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
IMU -- BNO055 9-axis on I2C (IO18=SDA, IO21=SCL, IO37=INT), addr 0x28; internal osc
BNO055 mid-line placement (user requirement): geometric center of rotation sensing. Mag data is calibration-grade only on a motor robot (1A at 5mm ~ Earth field); the yaw-rate loop uses the gyro. Fusion runs on-chip (100Hz NDOF) or raw gyro at 523Hz.
IR SENSOR ARRAY -- 6 wall sensors (direct ADC; line array + mux U4 removed)
ONE HEF4067 (line array only -- user decision 2026-07-15: wall sensors are read directly on ESP32 ADC1 pins). Each sensor: phototransistor (collector -> 47k pull-up to +3V3 AND to its readout node; emitter -> GND) + IR LED (anode -> current-limit resistor -> +3V3; cathode -> its GROUP's low-side sw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
WALL-SENSOR INDICATORS -- 6 top-side LEDs, LED ON = wall seen (PMOS, inverted node)
STATUS / POWER / RGB LEDs

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
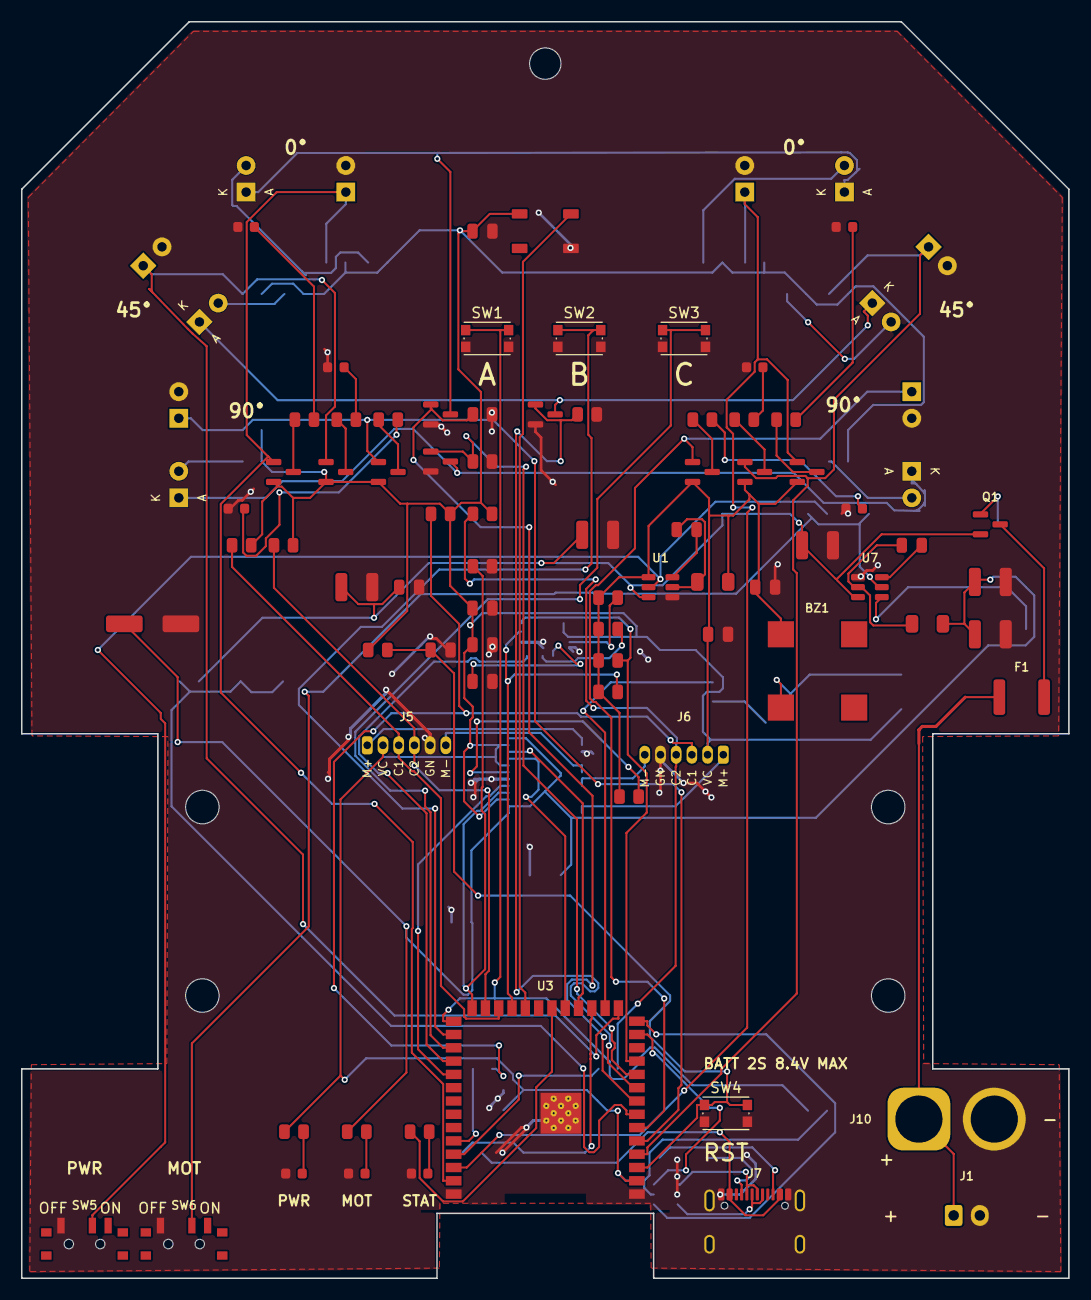
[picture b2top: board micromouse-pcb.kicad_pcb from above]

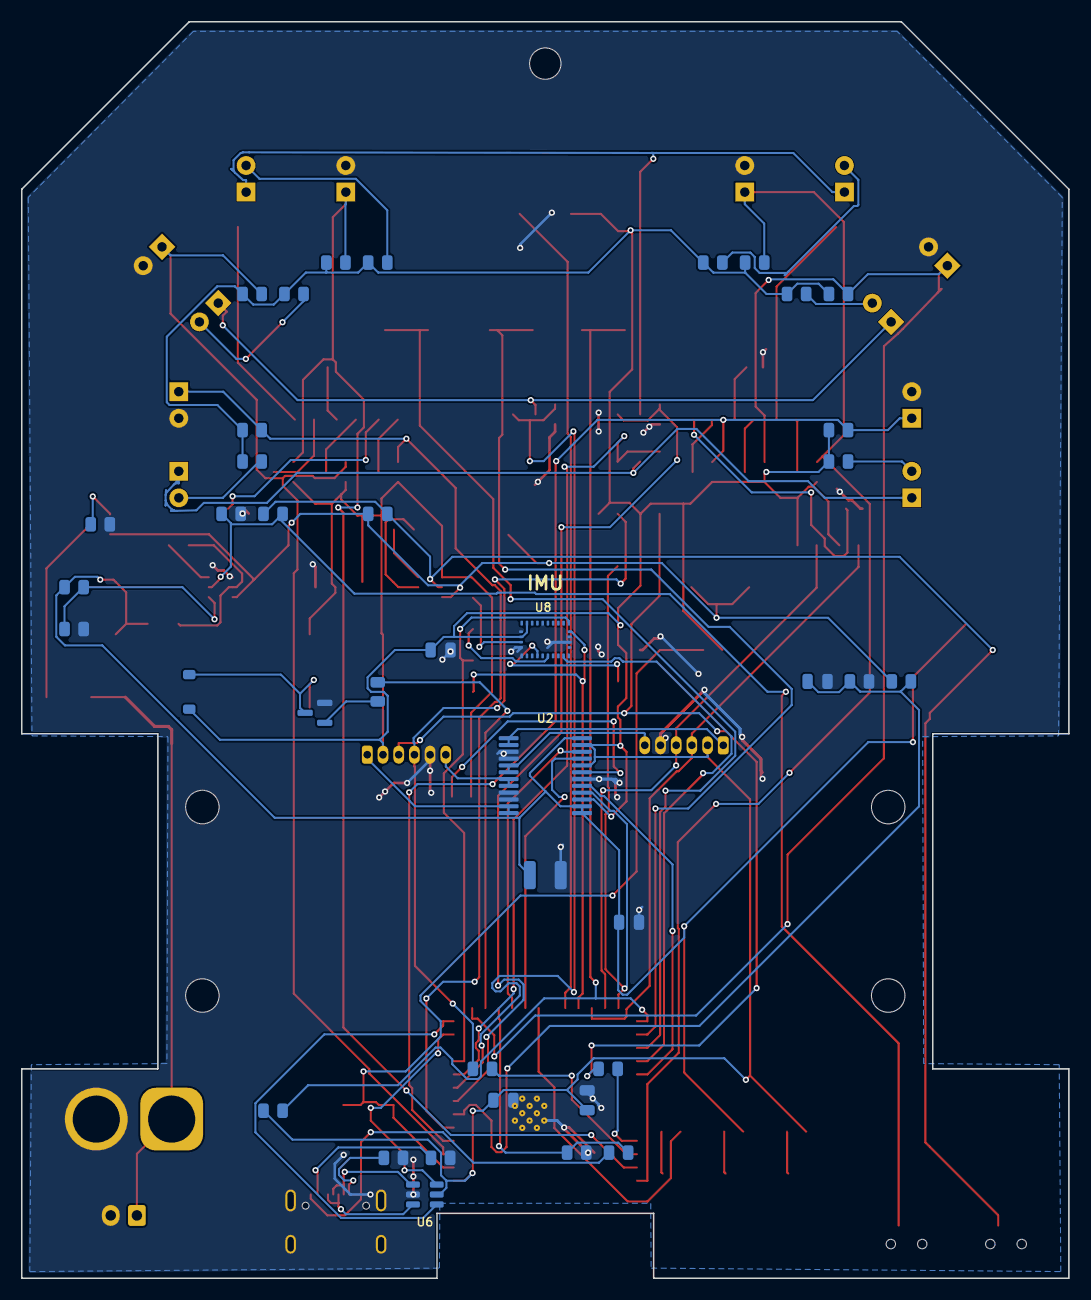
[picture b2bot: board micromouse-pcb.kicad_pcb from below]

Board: 2 copper layers, 100.0 x 120.0 mm, 135 parts (39 on the bottom side), 86 nets.

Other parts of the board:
H1, H2, H3, H4, H5: MountingHole_NPTH
MOT1, MOT2: N20_Motor_Encoder

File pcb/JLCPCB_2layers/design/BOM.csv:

Reference,Value,Footprint,Qty,MPN,Manufacturer
BZ1,"CMT-8504-100-SMT (magnetic transducer 8.5mm, 15R coil, 4kHz; pads 3/4 are mechanical dummies)",Buzzer_Beeper:MagneticBuzzer_CUI_CMT-8504-100-SMT,1,CMT-8504-100-SMT-TR,Same Sky (CUI Devices)
"C1,C4,C11,C18",10uF/25V,Capacitor_SMD:C_1210_3225Metric,4,CL32B106KBJNNNE,Samsung Electro-Mechanics
"C2,C3,C6,C8,C12,C14,C15,C20,C23,C31",100nF,Capacitor_SMD:C_0805_2012Metric,10,CL21B104KBCNNNC,Samsung Electro-Mechanics
"C5,C7",22uF,Capacitor_SMD:C_0805_2012Metric,2,CL21A226KPCLRNC,Samsung Electro-Mechanics
C9,1uF,Capacitor_SMD:C_0805_2012Metric,1,CL21B105KAFNNNE,Samsung Electro-Mechanics
"C10,C24",10uF,Capacitor_SMD:C_0805_2012Metric,2,CL21A106KPFNNNE,Samsung Electro-Mechanics
"C16,C17",22uF/25V,Capacitor_SMD:C_1210_3225Metric,2,CL32A226KAJNNNE,Samsung Electro-Mechanics
C30,220uF/16V,Capacitor_SMD:CP_Elec_6.3x7.7,1,EEE-FT1C221AP,Panasonic
"D1,D2,D3,D4,D5,D6",IR333-A (Everlight 5mm 940nm 20deg; LD271 base symbol; TSAL6400 is lifecycle-Obsolete at Lion),LED_THT:LED_D5.0mm_IRGrey,6,IR333-A,Everlight
"D23,D24,D25,D26,D27,D28,D30,D31,D33","Indicator LED 0603 super-red AlInGaP, high-eff bin (e.g. APT1608SURCK)",LED_SMD:LED_0603_1608Metric,9,APT1608SURCK,Kingbright
D29,1N4148W (flyback clamp across the buzzer coil),Diode_SMD:D_SOD-123,1,1N4148W-7-F,Diodes Incorporated
D32,WS2812B addressable RGB 5050 (JLC good-stock),LED_SMD:LED_WS2812B_PLCC4_5.0x5.0mm_P3.2mm,1,XL-5050RGBC-WS2812B,Xinglight
F1,2.6A/16V PPTC,Fuse:Fuse_1812_4532Metric,1,MINISMDC260F/16-2,Littelfuse
J1,BATT_IN_2S,Connector_JST:JST_XH_B2B-XH-A_1x02_P2.50mm_Vertical,1,B2B-XH-A,JST
"J5,J6",MOTOR_A_N20_ENCODER,Connector_JST:JST_ZH_B6B-ZR_1x06_P1.50mm_Vertical,2,B6B-ZR(LF)(SN),JST
J7,USB-C rear (GCT USB4105; VBUS unused -- battery powers the board),Connector_USB:USB_C_Receptacle_GCT_USB4105-xx-A_16P_TopMnt_Horizontal,1,USB4105-GF-A,GCT
J10,BATT_IN_XT60 (parallel option -- ONE PACK ONLY),Connector_AMASS:AMASS_XT60-M_1x02_P7.20mm_Vertical,1,XT60-M,AMASS
"L1,L2",4.7uH,n20:L_Bourns_SRP4020TA,2,SRP4020TA-4R7M,Bourns
Q1,"Q_PMOS reverse guard (DMP3098L-7: Vgs +/-20V, 2S-safe)",Package_TO_SOT_SMD:SOT-23,1,DMP3098L-7,Diodes Incorporated
"Q2,Q3,Q4,Q5,Q6,Q7",PT334-6B (5mm filtered PT; LONG LEAD = EMITTER; SFH309 base symbol so ERC checks pins),LED_THT:LED_D5.0mm_IRBlack,6,PT334-6B,Everlight
"Q16,Q17,Q18",BSS138 (real part; Q_NMOS_GSD base symbol used so ERC checks pins),Package_TO_SOT_SMD:SOT-23,3,BSS138LT1G,onsemi
"Q28,Q29,Q30,Q31,Q32,Q33",BSS84 (PMOS indicator driver; Q_PMOS base symbol),Package_TO_SOT_SMD:SOT-23,6,BSS84LT1G,onsemi
Q34,MMBT2222A (buzzer low-side driver; Q_NPN_BEC base symbol so ERC checks pins),Package_TO_SOT_SMD:SOT-23,1,MMBT2222A-7-F,Diodes Incorporated
"R1,R2,R62,R63,R64,R69,R73",100k,Resistor_SMD:R_0805_2012Metric,7,RC0805FR-07100KL,Yageo
R3,39k,Resistor_SMD:R_0805_2012Metric,1,RC0805FR-0739KL,Yageo
"R6,R7,R8,R9,R10,R11,R55,R65,R67,R79,R80",10k,Resistor_SMD:R_0805_2012Metric,11,WR08X1002FTL,Walsin
"R12,R56",5.1k,Resistor_SMD:R_0805_2012Metric,2,RC0805FR-075K1L,Yageo
"R13,R15,R17,R19,R21,R23",47k,Resistor_SMD:R_0805_2012Metric,6,RC0805FR-0747KL,Yageo
"R14,R16,R18,R20,R22,R24",33,Resistor_SMD:R_0805_2012Metric,6,RC0805FR-0733RL,Yageo
"R49,R50,R51,R52,R53,R54,R57,R58,R82,R83,R84",1k,Resistor_SMD:R_0805_2012Metric,11,RC0805FR-071KL,Yageo
R68,15k,Resistor_SMD:R_0805_2012Metric,1,RC0805FR-0715KL,Yageo
R70,220k,Resistor_SMD:R_0805_2012Metric,1,RC0805FR-07220KL,Yageo
R71,110k,Resistor_SMD:R_0805_2012Metric,1,RC0805FR-07110KL,Yageo
R74,11k,Resistor_SMD:R_0805_2012Metric,1,RC0805FR-0711KL,Yageo
"R77,R78",4.7k,Resistor_SMD:R_0805_2012Metric,2,RC0805FR-074K7L,Yageo
R81,220,Resistor_SMD:R_0805_2012Metric,1,RC0805FR-07220RL,Yageo
"SW1,SW2,SW3,SW4",Tactile pushbutton switch,Button_Switch_SMD:SW_Push_1P1T_NO_CK_KMR2,4,KMR221NGLFS,C&K
"SW5,SW6",PWR ALL (PCM12SMTR slide; slide-to-GND = OFF),Button_Switch_SMD:SW_SPDT_PCM12,2,PCM12SMTR,C&K
U1,AP63203WU-7 (fixed 3.3V 2A buck; AP63200WU base symbol so ERC checks pins),Package_TO_SOT_SMD:TSOT-23-6,1,AP63203WU-7,Diodes Incorporated
U2,TB6612FNG,Package_SO:SSOP-24_5.3x8.2mm_P0.65mm,1,"TB6612FNG,C,8,EL",Toshiba
U3,ESP32-S3-WROOM-1-N8R2 (quad PSRAM: IO35-37 usable; octal -R8 would lose them),RF_Module:ESP32-S3-WROOM-1,1,ESP32-S3-WROOM-1-N8R2,Espressif Systems
U6,USBLC6-2SC6 (SOT-23-6; 2P6 base symbol so ERC checks pins),Package_TO_SOT_SMD:SOT-23-6,1,USBLC6-2SC6,STMicroelectronics
U7,TPS54302DDCR (6.0V/3A motor buck; FB=100k/11k),Package_TO_SOT_SMD:SOT-23-6,1,TPS54302DDCR,Texas Instruments
U8,BNO055 (9-axis IMU + fusion; 3.3V native; I2C 0x28),n20:BNO055,1,BNO055,Bosch Sensortec
